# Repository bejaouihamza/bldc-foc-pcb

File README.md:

# FOC BLDC Motor Controller

> High-performance Field-Oriented Control driver built around the **STM32G474** MCU and **DRV8308** gate driver.

**[🌐 Live Project Page](https://bejaouihamza.github.io/bldc-foc-pcb/)**

[Kicanvas](https://kicanvas.org/?repo=https%3A%2F%2Fgithub.com%2Fsamuk%2Fbldc-foc-pcb%2Ftree%2Fmain%2Fkicad)

---

## Overview

This open-source hardware project is a compact, single-board FOC (Field-Oriented Control) motor driver designed for precision robotics, drones, CNC machines, and automation systems. It delivers smooth sinusoidal torque control with minimal audible noise thanks to Space Vector PWM (SVPWM) modulation.

| Spec | Value |
|------|-------|
| Input Voltage | 8.5V – 32V DC |
| Max Continuous Current | 50A |
| Peak Current | 100A (transient) |
| MCU | STM32G474CBTx (170 MHz, Cortex-M4) |
| Gate Driver | DRV8308 (SPI-configurable) |
| MOSFETs | 6× BSC098N10NS5 (100V, 9.8mΩ) |
| PWM Frequency | 20 kHz (center-aligned) |
| Commutation | Trapezoidal or 180° sinusoidal FOC |
| Sensors | 3× Hall differential inputs |
| Interface | USB-C + ARM SWD debug |

---

## Hardware

### PCB Layout (Top Layer)

The top layer shows the complete copper layout with phase outputs **U, V, W** at the top, power input (**XT60**) on the left, and the control section (STM32G474 + DRV8308) in the center. Note the star-grounding strategy and wide power traces for high-current paths.

### 3D Render

Compact form factor (~85mm × 55mm) with 4× M3 mounting holes. The large electrolytic capacitors handle bulk energy storage while the XT60 connector delivers main battery power.

### Schematic

The design is organized into clear functional blocks:
- **Power Input & Protection** — XT60 connector, fuse, reverse-polarity diode, LTC4359 ideal diode
- **5V Buck** — LM5164DDA switching regulator
- **3.3V LDO** — TLV75533 for clean logic supply
- **MCU** — STM32G474 with 24MHz crystal, USB-C, SWD, BOOT/RESET switches
- **FOC Unit** — DRV8308 gate driver with SPI configuration
- **Power Stage** — 6× BSC098N10NS5 MOSFETs in 3-phase bridge configuration
- **Hall Sensors** — 3× DRV5013 with 4.7kΩ pull-ups and VREG supply

---

## Architecture

### FOC Control Loop

```
                Speed Ref (ω*) → Speed PI → Iq*
                                ↓
                    ┌─────────────────┐
Id*=0 → Current PI  │  Inverse Park   │ → Vα,Vβ → SVPWM → DRV8308 → 3-Phase Bridge → Motor
  Iq → Current PI   │  (d-q → α-β)    │         ↑
                    └─────────────────┘         │
                            ↑                   │
  Hall → Estimator → θ,ω    │                   │
           ↑                │                   │
    Current Sense → Clarke → Park → Id,Iq (feedback)
```

The STM32G474 runs the full FOC algorithm:
1. **Speed PI** — compares reference vs. actual speed, outputs torque command
2. **Current PI (×2)** — regulates Id=0 and Iq=Iq* in the rotating d-q frame
3. **Inverse Park** — converts Vd,Vq → Vα,Vβ (rotating → stationary)
4. **SVPWM** — Space Vector modulation for 15% better DC bus utilization vs. sine PWM
5. **Feedback** — Hall sensors provide rotor position; 5mΩ shunt (R1) senses phase current

### Critical Pin Assignment

| Pin | Function | Connected To |
|-----|----------|--------------|
| **PA8** | TIM1_CH1 / CLKIN | DRV8308 CLKIN *(most important!)* |
| PA4-PA7 | SPI1 | DRV8308 SCS/SCLK/SDATAO/SDATAI |
| PB0 | DIRECTION | DRV8308 DIR |
| PB1 | SHDN | DRV8308 SHDN |
| PB7 | ENABLE | DRV8308 ENABLE |
| PB4 | FAULTn | DRV8308 FAULTn (input) |

> ⚠️ **TIM1_CH1 on PA8 is critical** — it synchronizes DRV8308 internal commutation timing. Moving it to a general-purpose timer breaks center-aligned PWM alignment.

---

## Firmware

### STM32 HAL Example

```c
/* Initialize DRV8308 for 180° sinusoidal FOC */
void DRV8308_Init(void) {
    // SYSOPT1: Enable sine mode
    DRV8308_WriteReg(DRV8308_SYSOPT1, 0x8000);  // SINMODE=1

    // SYSOPT2: 50mA gate drive for BSC098N10NS5
    DRV8308_WriteReg(DRV8308_SYSOPT2, 0x0300);  // IDRIVE=011

    // SYSOPT3: 1µs dead time
    DRV8308_WriteReg(DRV8308_SYSOPT3, 0x0040);

    // SYSOPT9: 50A overcurrent (0.25V / 5mΩ)
    DRV8308_WriteReg(DRV8308_SYSOPT9, 0x0000);
}

/* TIM1 center-aligned PWM for CLKIN */
void TIM1_PWM_Init(void) {
    htim1.Instance = TIM1;
    htim1.Init.Prescaler = 0;
    htim1.Init.CounterMode = TIM_COUNTERMODE_CENTERALIGNED1;
    htim1.Init.Period = 4250;  // 170MHz / (2×4250) = 20kHz
    // ...
    HAL_TIM_PWM_Start(&htim1, TIM_CHANNEL_1);
}
```

### Arduino / SimpleFOC

Also compatible with the [SimpleFOC](https://simplefoc.com/) library for rapid prototyping:

```cpp
BLDCMotor motor = BLDCMotor(11);  // 11 pole pairs
BLDCDriver3PWM driver = BLDCDriver3PWM(9, 10, 11, 8);
HallSensor sensor = HallSensor(2, 3, 4, 11);

motor.foc_modulation = FOCModulationType::SpaceVectorPWM;
motor.controller = MotionControlType::velocity;
motor.init();
motor.initFOC();
```

See the **[live project page](https://bejaouihamza.github.io/bldc-foc-pcb/)** for the complete code examples, wiring guide, and interactive SVPWM block diagram.

---

## Wiring

| Connection | Pin/Port | Notes |
|------------|----------|-------|
| Battery | XT60 | 8.5-32V DC |
| Motor U/V/W | Top screw terminals | Thick wire, high current |
| Hall VCC | VREG pin | 5V from DRV8308 |
| Hall GND | GND pin | Common ground |
| Hall signals | UHP/UHN, VHP/VHN, WHP/WHN | Differential pairs |
| Programming | SWD header | ST-Link V2/V3 |
| Serial/USB | USB-C | DFU bootloader + CDC |

---

## Bill of Materials (Key Components)

| Ref | Part | Description |
|-----|------|-------------|
| U1 | STM32G474CBTx | 170 MHz Cortex-M4 MCU |
| U2 | DRV8308 | 3-phase gate driver with SPI |
| Q1-Q6 | BSC098N10NS5 | 100V, 9.8mΩ N-channel MOSFET |
| U6 | LM5164DDA | 5V buck converter |
| U7 | TLV75533PDBV | 3.3V LDO |
| U8 | LTC4359 | Ideal diode controller |
| U3-U5 | DRV5013 | Hall sensors |
| Y1 | 24 MHz | Crystal oscillator |
| J1 | XT60PW-M | Battery connector |
| J5 | USB-C | USB 2.0 receptacle |

---

## Protection Features

- ✅ Reverse polarity (LTC4359 + diode)
- ✅ Overcurrent (cycle-by-cycle, 50A limit)
- ✅ Undervoltage lockout (UVLO)
- ✅ Overtemperature shutdown
- ✅ Rotor lock detection
- ✅ Fuse on battery input

---

## Getting Started

1. **Power up** — Connect 12-24V battery to XT60. Verify 5V and 3.3V LEDs.
2. **Connect motor** — Wire BLDC phases and Hall sensors.
3. **Flash firmware** — Use ST-Link on SWD header or DFU over USB-C.
4. **Configure DRV8308** — Run SPI init sequence (see code above).
5. **Spin** — Enable driver, set direction, send CLKIN frequency. Start at 100 Hz, ramp up slowly.

---

## Project Structure

```
bldc-foc-pcb/
├── README.md                          # Project overview and documentation
├── index.html                         # GitHub Pages project page
├── pcb-layout-top.png                 # Top-layer PCB layout
├── pcb-render.png                     # 3D render of the assembled PCB
├── schematic-full.png                 # Complete circuit schematic
├── bldc&foc motor controller.zip      # Complete KiCad project source
├── bldcfoc_motor_controller.zip       # Manufacturing files (Gerbers, drill, etc.)
├── bom.csv                            # Bill of Materials for assembly
├── designators.csv                    # Reference designator list
├── netlist.ipc                        # IPC-D-356 netlist for verification
└── positions.csv                      # Pick-and-place coordinates for SMT assembly
```

---

## License

Open source hardware. Feel free to use, modify, and distribute. Attribution appreciated.

---

**Designed by [bejaoui hamza](https://github.com/bejaouihamza)** · KiCad EDA 10.0.1

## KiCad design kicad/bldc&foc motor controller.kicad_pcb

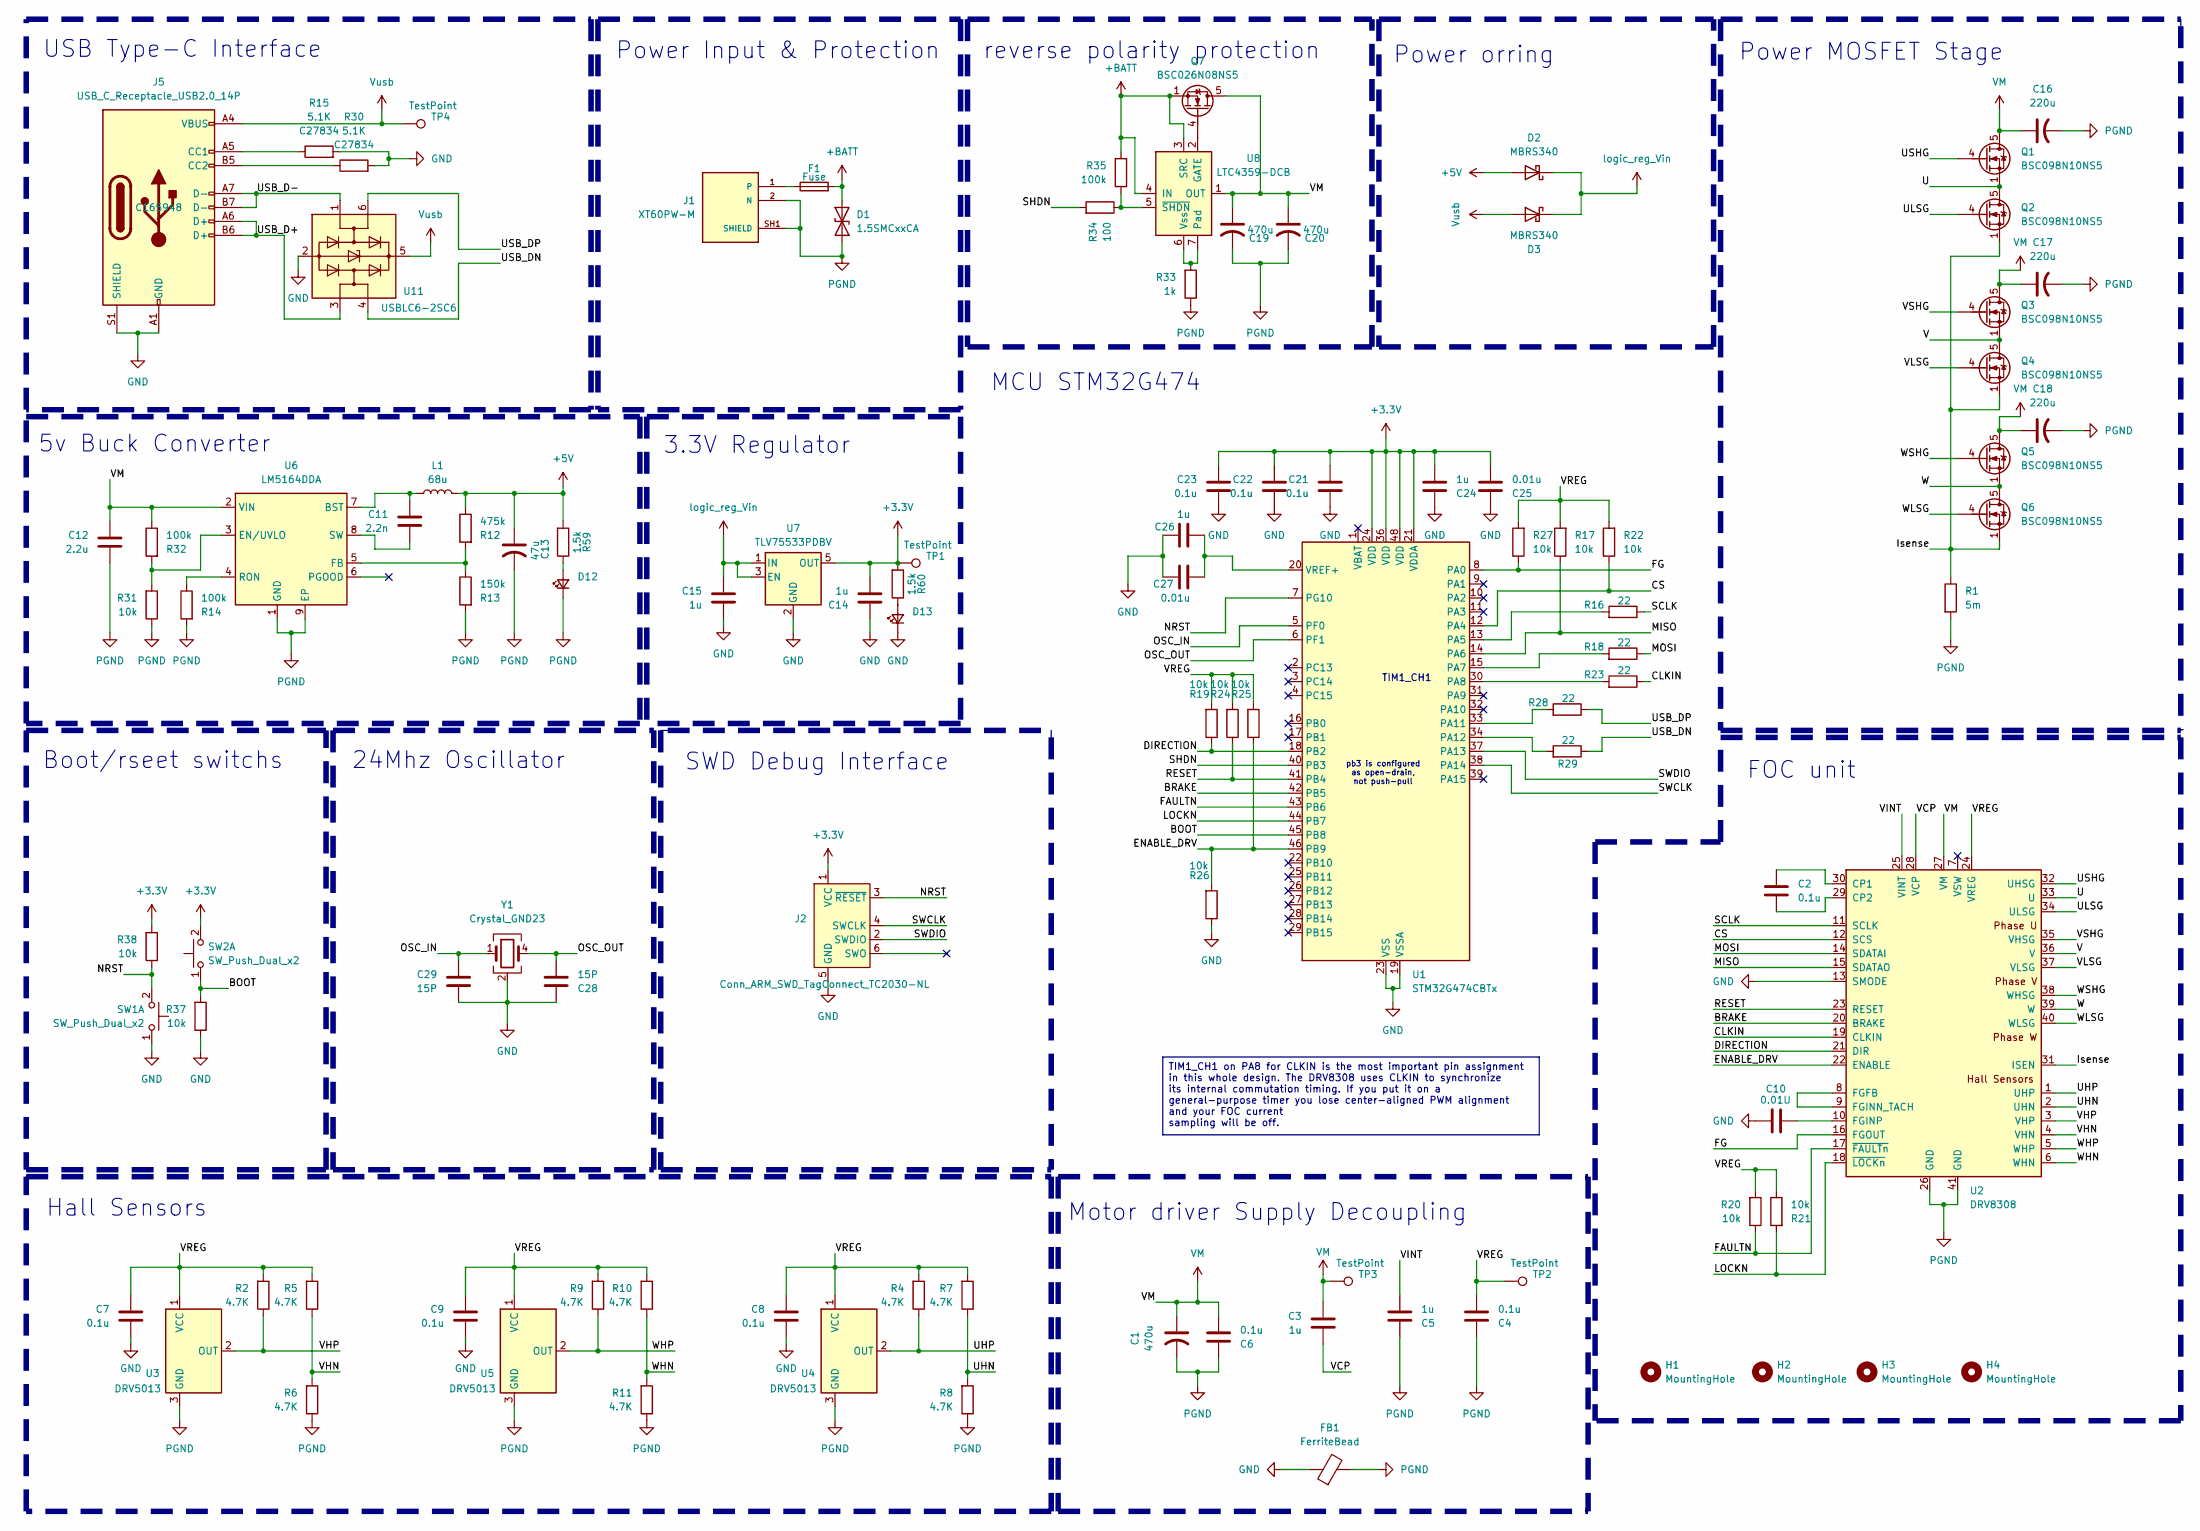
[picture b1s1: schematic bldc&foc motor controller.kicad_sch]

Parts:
C1, C19, C20: 470u; CP_Elec_8x10.5
C2, C4, C6, C7, C8, C9, C21, C22, C23: 0.1u; C_0603_1608Metric
C3, C5, C14, C15, C24, C26: 1u; C_0805_2012Metric
C10: 0.01U; C_0603_1608Metric
C11: 2.2n; C_0603_1608Metric
C12: 2.2u; C_0805_2012Metric
C13: 47u; CP_EIA-3528-21_Kemet-B
C16, C17, C18: 220u; CP_Elec_6.3x7.7
C25, C27: 0.01u; C_0603_1608Metric
C28, C29: 15P; C_0603_1608Metric
D1: 1.5SMCxxCA; D_SMC
D2, D3: MBRS340; D_SMC
D12, D13: LED_Small; LED_0805_2012Metric; LCSC Part # C2297
F1: Fuse; Fuse_Blade_Mini_directSolder
FB1: FerriteBead; L_1210_3225Metric
H1, H2, H3, H4: MountingHole; MountingHole_3.5mm_Pad_TopBottom
J1: XT60PW-M; AMASS_XT60PW-M; PARTREV 1.2
J2: Conn_ARM_SWD_TagConnect_TC2030-NL; Tag-Connect_TC2030-IDC-NL_2x03_P1.27mm_Vertical
J5: USB_C_Receptacle_USB2.0_14P; USB_C_Receptacle_HRO_TYPE-C-31-M-12; LCSC Part # C165948
L1: 68u; L_APV_ANR4012
Q1, Q2, Q3, Q4, Q5, Q6: BSC098N10NS5; TDSON-8-1
Q7: BSC026N08NS5; TDSON-8-1
R1: 5m; R_2512_6332Metric
R2, R4, R5, R6, R7, R8, R9, R10, R11: 4.7K; R_0603_1608Metric
R12: 475k; R_0603_1608Metric
R13: 150k; R_0603_1608Metric
R14, R32: 100k; R_0603_1608Metric
R15, R30: 5.1K; R_0603_1608Metric; LCSC Part # C27834
R16, R18, R23, R28, R29: 22; R_0603_1608Metric
R17, R19, R20, R21, R22, R24, R25, R26, R27, R31, R37: 10k; R_0603_1608Metric
R33: 1k; R_0603_1608Metric
R34: 100; R_0603_1608Metric
R35: 100k
R38: 10k
R59, R60: 1.5k; R_0402_1005Metric
SW1, SW2: SW_Push_Dual_x2; SW_TH_Tactile_Omron_B3F-100x
TP1, TP2, TP3, TP4: TestPoint; TestPoint_Pad_D1.5mm
U1: STM32G474CBTx; LQFP-48_7x7mm_P0.5mm
U2: DRV8308; Texas_RHA0040E_VQFN-40-1EP_6x6mm_P0.5mm_EP3.52x2.62mm
U3, U4, U5: DRV5013; SOT-23
U6: LM5164DDA; HSOP-8-1EP_3.9x4.9mm_P1.27mm_EP2.41x3.1mm_ThermalVias
U7: TLV75533PDBV; SOT-23-5
U8: LTC4359-DCB; DFN-6-1EP_3x2mm_P0.5mm_EP1.65x1.35mm
U11: USBLC6-2SC6; SOT-23-6; Manufacturer_Part_Number USBLC6-2SC6; Mouser Part Number 511-USBLC6-2SC6
Y1: Crystal_GND23; Crystal_SMD_3225-4Pin_3.2x2.5mm

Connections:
+3.3V: C14.2, C21.1, C22.1, C23.1, C24.2, C25.2, J2.1 (VCC), R38.2, R60.2, SW2.2 (D), TP1.1 (1_1), U1.21 (VDDA), U1.24 (VDD), U1.36 (VDD), U1.48 (VDD), U7.5 (OUT)
+5V: C13.1, D2.2 (A), L1.2, R12.1, R59.2
+BATT: D1.1 (A1), F1.2, Q7.1 (S), Q7.2 (S), Q7.3 (S), R35.2, U8.3 (SRC), U8.4 (IN)
/BOOT: R37.2, SW2.1 (C), U1.45 (PB8)
/BRAKE: U1.42 (PB5), U2.20 (BRAKE)
/CLKIN: R23.1, U2.19 (CLKIN)
/CS: R22.1, U1.12 (PA4), U2.12 (SCS)
/DIRECTION: R19.1, U1.18 (PB2), U2.21 (DIR)
/ENABLE_DRV: R25.1, R26.2, U1.46 (PB9), U2.22 (ENABLE)
/FAULTN: R20.1, U1.43 (PB6), U2.17 (~FAULTn)
/FG: R27.1, U1.8 (PA0), U2.16 (FGOUT)
/Isense: Q2.1 (S), Q2.2 (S), Q2.3 (S), Q4.1 (S), Q4.2 (S), Q4.3 (S), Q6.1 (S), Q6.2 (S), Q6.3 (S), R1.1, U2.31 (ISEN)
/LOCKN: R21.2, U1.44 (PB7), U2.18 (~LOCKn)
/MISO: R17.1, U1.14 (PA6), U2.15 (SDATAO)
/MOSI: R18.1, U2.14 (SDATAI)
/NRST: J2.3 (~RESET), R38.1, SW1.2 (D), U1.7 (PG10)
/OSC_IN: C29.1, U1.5 (PF0), Y1.1
/OSC_OUT: C28.2, U1.6 (PF1), Y1.4
/RESET: R24.1, U1.41 (PB4), U2.23 (RESET)
/SCLK: R16.1, U2.11 (SCLK)
/SHDN: R34.2, U1.40 (PB3)
/SWCLK: J2.4 (SWCLK), U1.38 (PA14)
/SWDIO: J2.2 (SWDIO), U1.37 (PA13)
/U: Q1.1 (S), Q1.2 (S), Q1.3 (S), Q2.5 (D), U2.33 (U)
/UHN: R7.1, R8.2, U2.2 (UHN)
/UHP: R4.1, U2.1 (UHP), U4.2 (OUT)
/ULSG: Q2.4 (G), U2.34 (ULSG)
/USB_D+: J5.A6 (D+), J5.B6 (D+), U11.3 (I/O2)
/USB_D-: J5.A7 (D-), J5.B7 (D-), U11.1 (I/O1)
/USB_DN: R29.1, U11.4 (I/O2)
/USB_DP: R28.1, U11.6 (I/O1)
/USHG: Q1.4 (G), U2.32 (UHSG)
/V: Q3.1 (S), Q3.2 (S), Q3.3 (S), Q4.5 (D), U2.36 (V)
/VCP: C3.2, U2.28 (VCP)
/VHN: R5.1, R6.2, U2.4 (VHN)
/VHP: R2.1, U2.3 (VHP), U3.2 (OUT)
/VINT: C5.2, U2.25 (VINT)
/VLSG: Q4.4 (G), U2.37 (VLSG)
/VREG: C4.2, C7.1, C8.1, C9.1, R2.2, R4.2, R5.2, R7.2, R9.2, R10.2, R17.2, R19.2, R20.2, R21.1, R22.2, R24.2, R25.2, R27.2, TP2.1 (1_1), U2.24 (VREG), U3.1 (VCC), U4.1 (VCC), U5.1 (VCC)
/VSHG: Q3.4 (G), U2.35 (VHSG)
/W: Q5.1 (S), Q5.2 (S), Q5.3 (S), Q6.5 (D), U2.39 (W)
/WHN: R10.1, R11.2, U2.6 (WHN)
/WHP: R9.1, U2.5 (WHP), U5.2 (OUT)
/WLSG: Q6.4 (G), U2.40 (WLSG)
/WSHG: Q5.4 (G), U2.38 (WHSG)
GND: C7.2, C8.2, C9.2, C10.2, C14.1, C15.2, C21.2, C22.2, C23.2, C24.1, C25.1, C26.1, C27.1, C28.1, C29.2, D13.1 (K), FB1.1, J2.5 (GND), J5.A1 (GND), J5.A12 (GND), J5.B1 (GND), J5.B12 (GND), J5.S1 (SHIELD), R15.2, R26.1, R30.2, R37.1, SW1.1 (C), U1.19 (VSSA), U1.23 (VSS), U1.35 (VSS), U1.47 (VSS), U2.13 (SMODE), U7.2 (GND), U11.2 (GND), Y1.2 (G), Y1.3 (G)
unnamed: D12.2 (A), R59.1
unnamed: D13.2 (A), R60.1
unnamed: F1.1, J1.1
unnamed: J5.A5 (CC1), R15.1
unnamed: J5.B5 (CC2), R30.1
unnamed: Q7.4 (G), U8.2 (GATE)
unnamed: R16.2, U1.13 (PA5)
unnamed: R18.2, U1.15 (PA7)
unnamed: R23.2, U1.30 (PA8)
unnamed: R28.2, U1.33 (PA11)
unnamed: R29.2, U1.34 (PA12)
unnamed: C26.2, C27.2, U1.20 (VREF+)
unnamed: C2.1, U2.30 (CP1)
unnamed: C2.2, U2.29 (CP2)
unnamed: U2.8 (FGFB), U2.9 (FGINN_TACH)
unnamed: C10.1, U2.10 (FGINP)
unnamed: C11.1, L1.1, U6.7 (BST)
unnamed: R31.2, R32.2, U6.3 (EN/UVLO)
unnamed: R12.2, R13.1, U6.5 (FB)
unnamed: R14.1, U6.4 (RON)
unnamed: C11.2, U6.8 (SW)
unnamed: R33.2, U8.6 (Vss), U8.7 (Pad)
unnamed: R34.1, R35.1, U8.5 (~SHDN)
PGND: C1.2, C4.1, C5.1, C6.1, C12.2, C13.2, C16.2, C17.2, C18.2, C19.2, C20.2, D1.2 (A2), D12.1 (K), FB1.2, J1.2 (N), J1.SH1 (SHIELD), J1.SH2 (SHIELD), R1.2, R6.1, R8.1, R11.1, R13.2, R14.2, R31.1, R33.1, U2.26 (GND), U2.41 (GND), U3.3 (GND), U4.3 (GND), U5.3 (GND), U6.1 (GND), U6.9 (EP)
VM: C1.1, C3.1, C6.2, C12.1, C16.1, C17.1, C18.1, C19.1, C20.1, Q1.5 (D), Q3.5 (D), Q5.5 (D), Q7.5 (D), R32.1, TP3.1 (1_1), U2.27 (VM), U6.2 (VIN), U8.1 (OUT)
Vusb: D3.2 (A), J5.A4 (VBUS), J5.A9 (VBUS), J5.B4 (VBUS), J5.B9 (VBUS), TP4.1 (1_1), U11.5 (VBUS)
logic_reg_Vin: C15.1, D2.1 (K), D3.1 (K), U7.1 (IN), U7.3 (EN)

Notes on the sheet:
pb3 is configured as open-drain, not push-pull
3.3V Regulator
USB Type-C Interface
Boot/rseet switchs
Power MOSFET Stage
24Mhz Oscillator
MCU STM32G474
Power Input & Protection
reverse polarity protection
TIM1_CH1
SWD Debug Interface
Motor driver Supply Decoupling
Hall Sensors
5v Buck Converter
FOC unit
Power orring
TIM1_CH1 on PA8 for CLKIN is the most important pin assignment in this whole design. The DRV8308 uses CLKIN to synchronize its internal commutation timing. If you put it on a general-purpose timer you lose center-aligned PWM alignment and your FOC current sampling will be off.

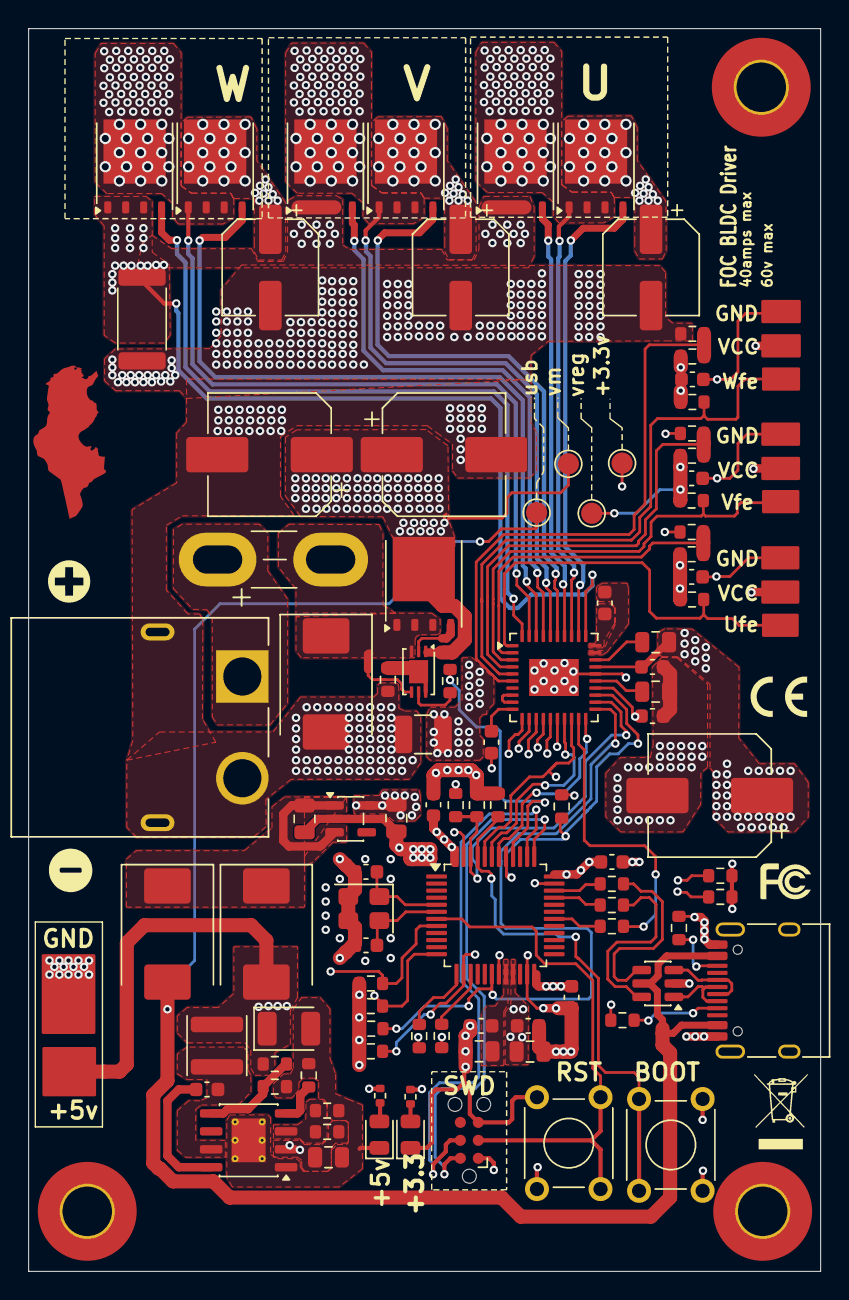
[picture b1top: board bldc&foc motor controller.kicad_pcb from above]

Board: 6 copper layers, 56.1 x 88.0 mm, 99 parts (0 on the bottom side), 73 nets.

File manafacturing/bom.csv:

Designator,Footprint,Quantity,Value,LCSC Part #
"C1, C19, C20",CP_Elec_8x10.5,3,470u,
"C10, C25, C27",0603,3,0.01U,
C11,0603,1,2.2n,
C12,0805,1,2.2u,
C13,CP_EIA-3528-21_Kemet-B,1,47u,
"C14, C15, C24, C26, C3, C5",0805,6,1u,
"C16, C17, C18",CP_Elec_6.3x7.7,3,220u,
"C2, C21, C22, C23, C4, C6, C7, C8, C9",0603,9,0.1u,
"C28, C29",0603,2,15P,
D1,D_SMC,1,1.5SMCxxCA,
"D12, D13",0805,2,LED_Small,C2297
"D2, D3",D_SMC,2,MBRS340,
F1,Fuse_Blade_Mini_directSolder,1,Fuse,
FB1,1210,1,FerriteBead,
J1,AMASS_XT60PW-M,1,XT60PW-M,
J5,USB_C_Receptacle_HRO_TYPE-C-31-M-12,1,USB_C_Receptacle_USB2.0_14P,C165948
L1,L_APV_ANR4012,1,68u,
"Q1, Q2, Q3, Q4, Q5, Q6",TDSON-8-1,6,BSC098N10NS5,
Q7,TDSON-8-1,1,BSC026N08NS5,
R1,2512,1,5m,
"R10, R11, R2, R4, R5, R6, R7, R8, R9",0603,9,4.7K,
R12,0603,1,475k,
R13,0603,1,150k,
"R14, R32",0603,2,100k,
"R15, R30",0603,2,5.1K,C27834
"R16, R18, R23, R28, R29",0603,5,22,
"R17, R19, R20, R21, R22, R24, R25, R26, R27, R31, R37",0603,11,10k,
R33,0603,1,1k,
R34,0603,1,100,
"R59, R60",0402,2,1.5k,
"SW1, SW2",SW_TH_Tactile_Omron_B3F-100x,2,SW_Push_Dual_x2,
"TP1, TP2, TP3, TP4",TestPoint_Pad_D1.5mm,4,TestPoint,
U1,LQFP-48_7x7mm_P0.5mm,1,STM32G474CBTx,
U11,SOT-23-6,1,USBLC6-2SC6,
U2,Texas_RHA0040E_VQFN-40-1EP_6x6mm_P0.5mm_EP3.52x2.62mm,1,DRV8308,
U6,HSOP-8-1EP_3.9x4.9mm_P1.27mm_EP2.41x3.1mm_ThermalVias,1,LM5164DDA,
U7,SOT-23-5,1,TLV75533PDBV,
U8,DFN-6-1EP_3x2mm_P0.5mm_EP1.65x1.35mm,1,LTC4359-DCB,
Y1,Crystal_SMD_3225-4Pin_3.2x2.5mm,1,Crystal_GND23,
